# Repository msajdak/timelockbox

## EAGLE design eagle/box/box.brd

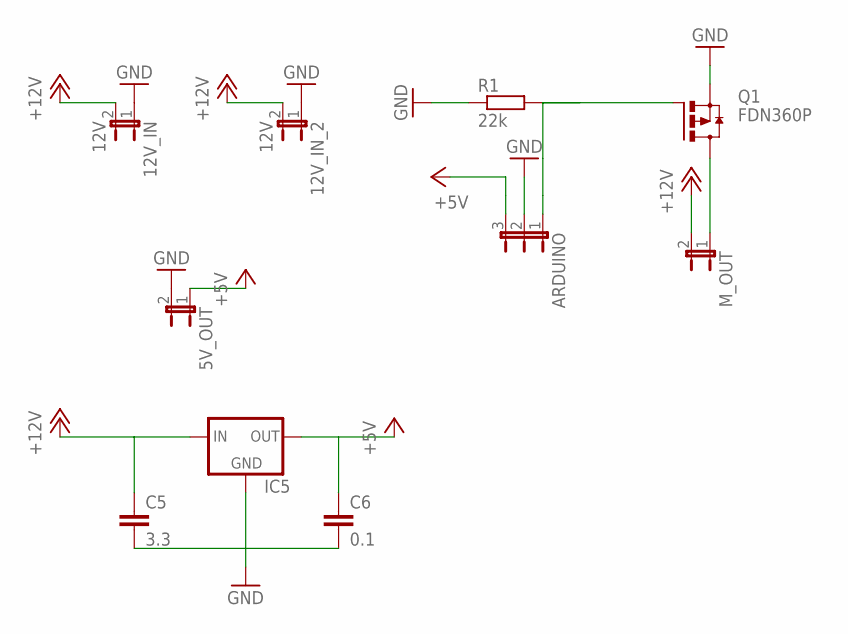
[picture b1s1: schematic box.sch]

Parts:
5V_OUT: JP1E; JP1
12V_IN, 12V_IN_2: 12V; JP1
ARDUINO: JP2E; JP2
C5: 3.3; C025-024X044
C6: 0.1; C025-024X044
IC5: 78XXL
M_OUT: JP1E; JP1
Q1: FDN360P; SUPER-SOT3
R1: 22k; 0204/7

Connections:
+5V: 5V_OUT.1, ARDUINO.3, C6.1, IC5.OUT
+12V: 12V_IN.2, 12V_IN_2.2, C5.1, IC5.IN, M_OUT.2
GND: 5V_OUT.2, 12V_IN.1, 12V_IN_2.1, ARDUINO.2, C5.2, C6.2, IC5.GND, Q1.2 (S), R1.1
unnamed: M_OUT.1, Q1.3 (D)
unnamed: ARDUINO.1, Q1.1 (G), R1.2

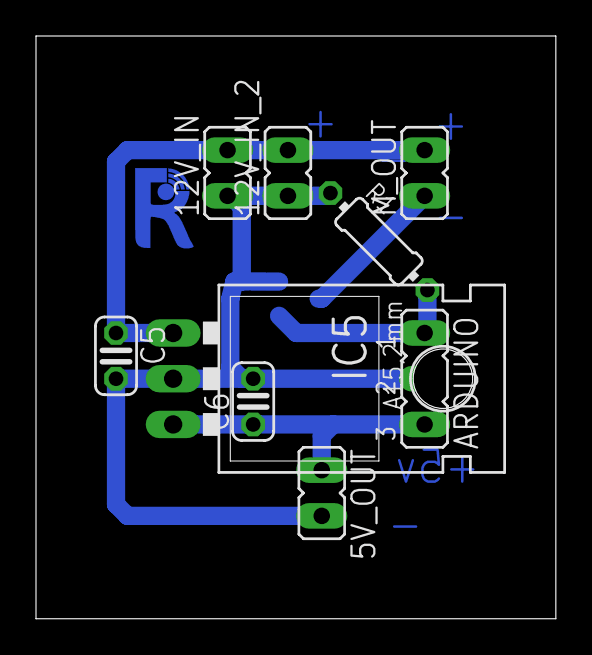
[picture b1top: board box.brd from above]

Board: 2 copper layers, 28.9 x 32.4 mm, 10 parts (1 on the bottom side), 5 nets.

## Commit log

2017-08-07 add eag;e
2017-10-05 next
